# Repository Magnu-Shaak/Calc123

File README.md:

# Numpad
Making a Numpad accessory that also works as a stand-alone calculator!

Features:
- Numberpad (0-9, 4 operations,"=", ".")
    + Has a built in Local Calculator that displays on the OLED
- Custom Shortcuts Layer
- Displays Layer on OLED
    + Use it yourself: Info at [https://github.com/Magnu-Shaak/Calc123/blob/main/oled_extention.md](url)

3d render in Onshape

## BOM
Also available at [https://github.com/Magnu-Shaak/Calc123/blob/main/bom.csv](url)
| Item                      | Quantity | Listed Price | Total Cost | Link                                                                                  | Source        | Notes                                                                    |         |
|---------------------------|----------|--------------|------------|---------------------------------------------------------------------------------------|---------------|--------------------------------------------------------------------------|---------|
| PCB (5 piece)             | 1        | 4            | 5.76       |                                                                                       | JLC PCB       | Together with another order, paying with JLC account (Saves on shipping) |         |
| XIAO RP2040               | 1        | 4.9          | 4.9        | https://www.digikey.com/en/products/detail/seeed-technology-co-ltd/102010428/14672129 | DigiKey       |                                                                          |         |
| Diodes                    | 16       | 0.8          | 0.8        | https://www.digikey.com/en/products/detail/diotec-semiconductor/1N4148/13164514       | DigiKey       |                                                                          |         |
| "Switches                 |          |              |            |                                                                                       |               |                                                                          |         |
| (32 piece)"               | 1        | 10.99        | 10.99      | https://www.amazon.com/gp/aw/d/B09NNN4XPB                                             | Amazon        | Cheaper than AliExpress                                                  |         |
| 0.91 in. OLED (2 piece)   | 1        | 5.99         | 0          | https://www.amazon.com/Dorhea-Display-Module-SSD1306-3-3V-5V/dp/B08F9F8BYB            | Amazon        | Cheaper than Digikey with manu. Shipping. Can pay for myself             |         |
|                           |          |              |            |                                                                                       |               |                                                                          |         |
| Soldering Iron (Pinecil)* | 1        | 39.99        | 39.99      | https://www.amazon.com/PINECIL-Smart-Mini-Portable-Soldering/dp/B096X6SG13            | Amazon        | Cheapest Adjustable Soldering Iron                                       |         |
| Solder (0.5 oz)           | 1        | 2.97         | 2.97       | https://www.digikey.com/en/products/detail/chip-quik-inc/NCSW-031-0-5OZ/13531391      | DigiKey       | 63/37 tin-lead solder (0.031"")                                          |         |
| De-soldering Braid        | 1        | 2.59         | 2.59       | https://www.digikey.com/en/products/detail/chip-quik-inc/SOLDERWICK2-0/14636561       | DigiKey       | 0.08"                                                                    | 5 foot" |
| Soldering Stand & Sponge  | 1        | 3.28         | 3.28       | https://www.digikey.com/en/products/detail/soldered-electronics/555024/29271457       | Digikey       | Soldered Electronics: ""Soldering Iron Stand""                           |         |
|                           |          |              |            |                                                                                       |               |                                                                          |         |
| Case                      | 1        | 3.5          | 0          |                                                                                       | Local Library | $0.05 per gram, will pay for myself                                      |         |
| Key Caps (10 piece)       | 2        | 9.9          | 9.9        | https://www.digikey.com/en/products/detail/adafruit-industries-llc/5039/14313478      | DigiKey       | Adafruit, cheaper than singles                                           |         |
|                           |          |              |            |                                                                                       |               |                                                                          |         |
| M2 screw (16mm)           | 5        | 0.65         | 0.65       | http://digikey.com/en/products/detail/essentra-components/50M020040P016B/26883690     | DigiKey       | Essentra Components, 5th one was 1 cent                                  |         |
| M2 heatset Inserts        | 5        | 1.09         | 1.09       | https://www.digikey.com/en/products/detail/tri-star-industries-inc/M20X157C/13535373  | DigiKey       | Edit 3d model, 5th one was 1 cent                                        |         |
|                           |          |              |            |                                                                                       |               |                                                                          |         |
| DigiKey: Shipping and Tax | 8 (32)   | 9.09         | 10.45      | https://www.digikey.com/ordering/shoppingcart                                         | DigiKey       | Shipping with USPS Ground Advantage (4.99)                               |         |
| Amazon: Shipping and Tax  | s        | 3.82         | 3.82       |                                                                                       | Amazon        | Free shipping with prime                                                 |         |
|                           |          |              |            |                                                                                       |               |                                                                          |         |
| Total                     | 71       | 103.56       | 97.19      |                                                                                       |               |                                                                          |         |

## Demo links

PCB Demo [Link](https://kicanvas.org/?repo=https%3A%2F%2Fgithub.com%2FMagnu-Shaak%2FCalc123%2Ftree%2Fmain%2FPCB)

OnShape Demo [Link](https://cad.onshape.com/documents/84cb760b87cada0103a9576e/w/b2684d83a2c2c7ea59db64e2/e/a0996dbd1c890850b6caf7a1?renderMode=0&uiState=6a6621498755df13821d28c6)
(click on search bar and hit enter again to load properly)

Code is visible under the Firmware folder

## Asembly

BOM (Bill of Materials) - above, or at [https://github.com/Magnu-Shaak/Calc123/blob/main/BOM.csv](url)

0 - Gather your Materials (PCB, Case parts, Devboard, and a usb-c to [something] cable to connect to your computer

1 - Download Circuit Python (v9.2.9) from circuitpython.org for the microcontroller [here](https://adafruit-circuit-python.s3.amazonaws.com)

2 - Download KMK (as .zip) from the kmk_firmware repo on github [here](https://github.com/KMKfw/kmk_firmware)

3 - Download the dependency files from the circuitpython.org/libraries (for the circuit python 9.x version) or from [here](https://github.com/adafruit/Adafruit_CircuitPython_Bundle/releases/download/20260729/adafruit-circuitpython-bundle-9.x-mpy-20260729.zip)

4 - Download "main.py" and "oled_extension.py" from this repo. They are stored under the "Production" Folder

5 - Mount the microcontroller to your computer
    -Hold the 'B' (boot) bottom
    -Connect it to the computer via a usb-c to [anything on your computer] cable
    -Release the 'B' bottom

6 - Upload Circuit Python's .u2f file onto the microcontroller
    -It Should self eject and reconnect as CIRCUITPY

7 - From the kmk_firmware zip file, Upload the "KMK" folder and boot.py into the root of the CIRCUITPY drive

8.5 - If there is not already a "lib" folder in the root of your CIRCUITPY drive, make one

9 - From the circuit python bundle zip file, Upload the "adafruit_bus_device" and "adafruit_display_text" folders and "adafruit_displayio_ssd1306" file into the lib folder of your CIRCUITPY drive

10 - Eject your CIRCUITPY drive, and disconnect your microcontroller from your computer.

11 - Solder your XIAO RP 2040 devboard and 16 diodes (make sure they are oriented correctly) to the back of your PCB

12 - Place the Top Plate onto the front of your PCB, and align it with the mx key switch positions

13 - Solder the Key switches to the PCB on the back. The plate should be supported by the mx switches when you flip back over

14 - Install the Heatset Inserts to the bottom of your Case

15 - Place the PCB and Top Plate onto the supports in the case

16 - Screw the plate onto your PCB

16.5 - Add the Key Caps onto the MX Switches

17 - Slide in the Custom Insert
16 - Connect your Macropad to the computer and begin using it.

## All Images

  Schematic (Controller)

  Schematic (Key Array)

  PCB Design (KiCad)

  PCB Render (KiCad)

  Case (Onshape)

  USB Cutout

  Custom Insert (Onshape)

  Code is under Firmware/main.py and Firmware/oled_extension.py

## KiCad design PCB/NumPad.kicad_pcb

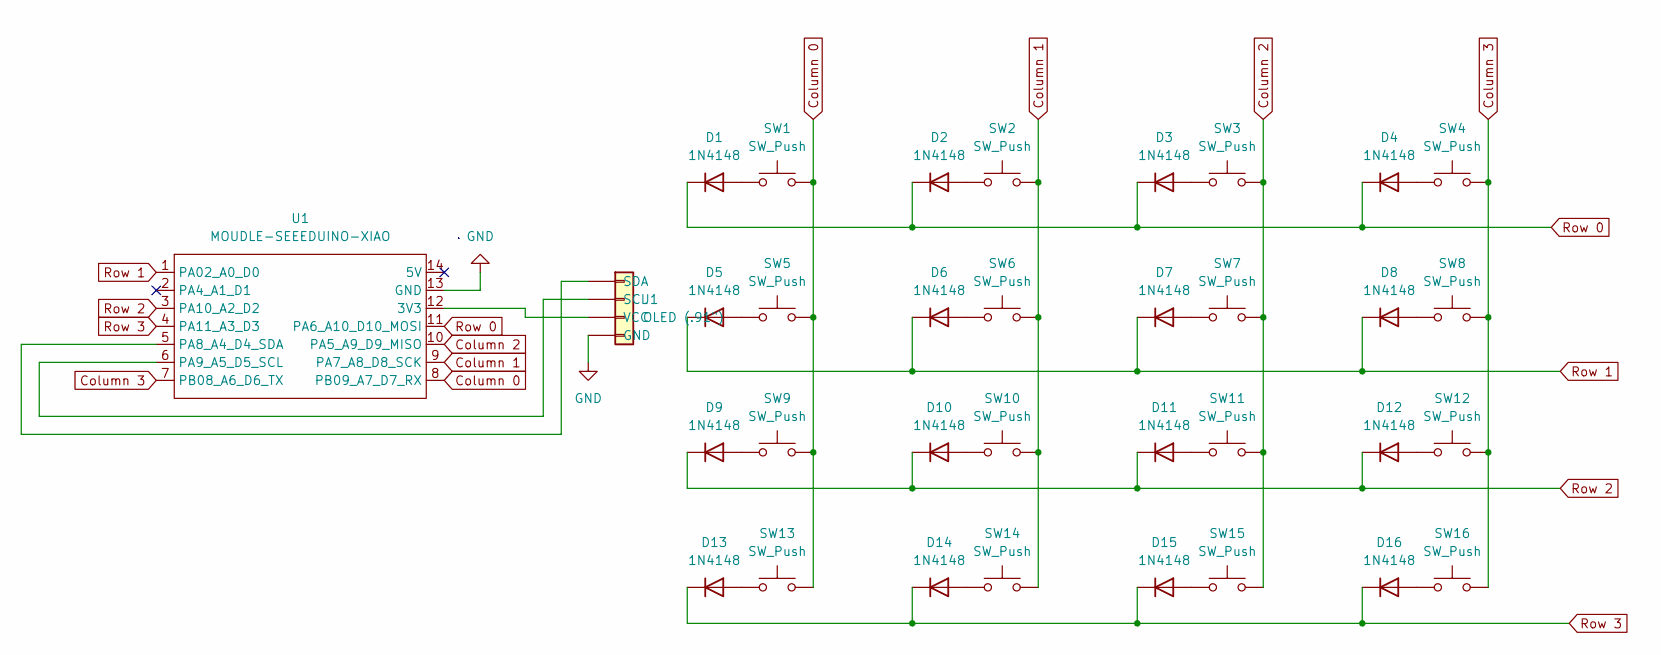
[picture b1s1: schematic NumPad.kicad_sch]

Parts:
D1, D2, D3, D4, D5, D6, D7, D8, D9, D10, D11, D12, D13, D14, D15, D16: 1N4148; D_DO-35_SOD27_P7.62mm_Horizontal
J1: OLED (.91"); 0.91_inch_OLED
SW1, SW2, SW3, SW4, SW5, SW6, SW7, SW8, SW9, SW10, SW11, SW12, SW13, SW14, SW15, SW16: SW_Push; SW_Cherry_MX_1.00u_PCB(1)
U1: MOUDLE-SEEEDUINO-XIAO; XIAO-Generic-Hybrid-14P-2.54-21X17.8MM

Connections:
Column 0: SW1.2, SW5.2, SW9.2, SW13.2, U1.8 (PB09_A7_D7_RX)
Column 1: SW2.2, SW6.2, SW10.2, SW14.2, U1.9 (PA7_A8_D8_SCK)
Column 2: SW3.2, SW7.2, SW11.2, SW15.2, U1.10 (PA5_A9_D9_MISO)
Column 3: SW4.2, SW8.2, SW12.2, SW16.2, U1.7 (PB08_A6_D6_TX)
GND: J1.1 (GND), U1.13 (GND)
unnamed: D1.2 (A), SW1.1
unnamed: D2.2 (A), SW2.1
unnamed: D3.2 (A), SW3.1
unnamed: D4.2 (A), SW4.1
unnamed: D5.2 (A), SW5.1
unnamed: D6.2 (A), SW6.1
unnamed: D7.2 (A), SW7.1
unnamed: D8.2 (A), SW8.1
unnamed: D9.2 (A), SW9.1
unnamed: D10.2 (A), SW10.1
unnamed: D11.2 (A), SW11.1
unnamed: D12.2 (A), SW12.1
unnamed: D13.2 (A), SW13.1
unnamed: D14.2 (A), SW14.1
unnamed: D15.2 (A), SW15.1
unnamed: D16.2 (A), SW16.1
unnamed: J1.3 (SCL), U1.6 (PA9_A5_D5_SCL)
unnamed: J1.4 (SDA), U1.5 (PA8_A4_D4_SDA)
unnamed: J1.2 (VCC), U1.12 (3V3)
Row 0: D1.1 (K), D2.1 (K), D3.1 (K), D4.1 (K), U1.11 (PA6_A10_D10_MOSI)
Row 1: D5.1 (K), D6.1 (K), D7.1 (K), D8.1 (K), U1.1 (PA02_A0_D0)
Row 2: D9.1 (K), D10.1 (K), D11.1 (K), D12.1 (K), U1.3 (PA10_A2_D2)
Row 3: D13.1 (K), D14.1 (K), D15.1 (K), D16.1 (K), U1.4 (PA11_A3_D3)

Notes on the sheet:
GND

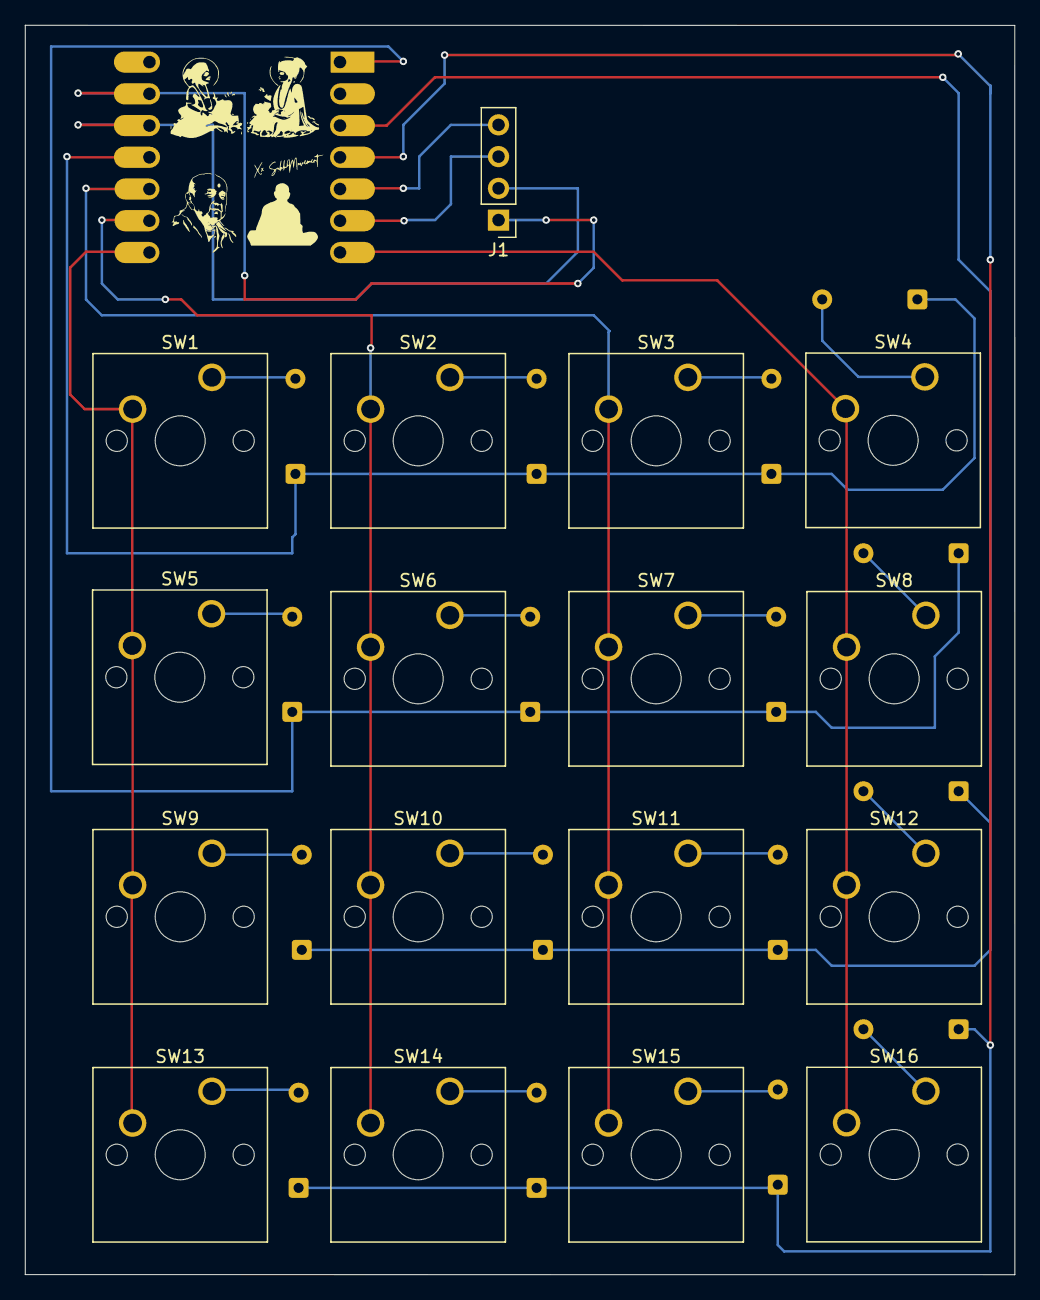
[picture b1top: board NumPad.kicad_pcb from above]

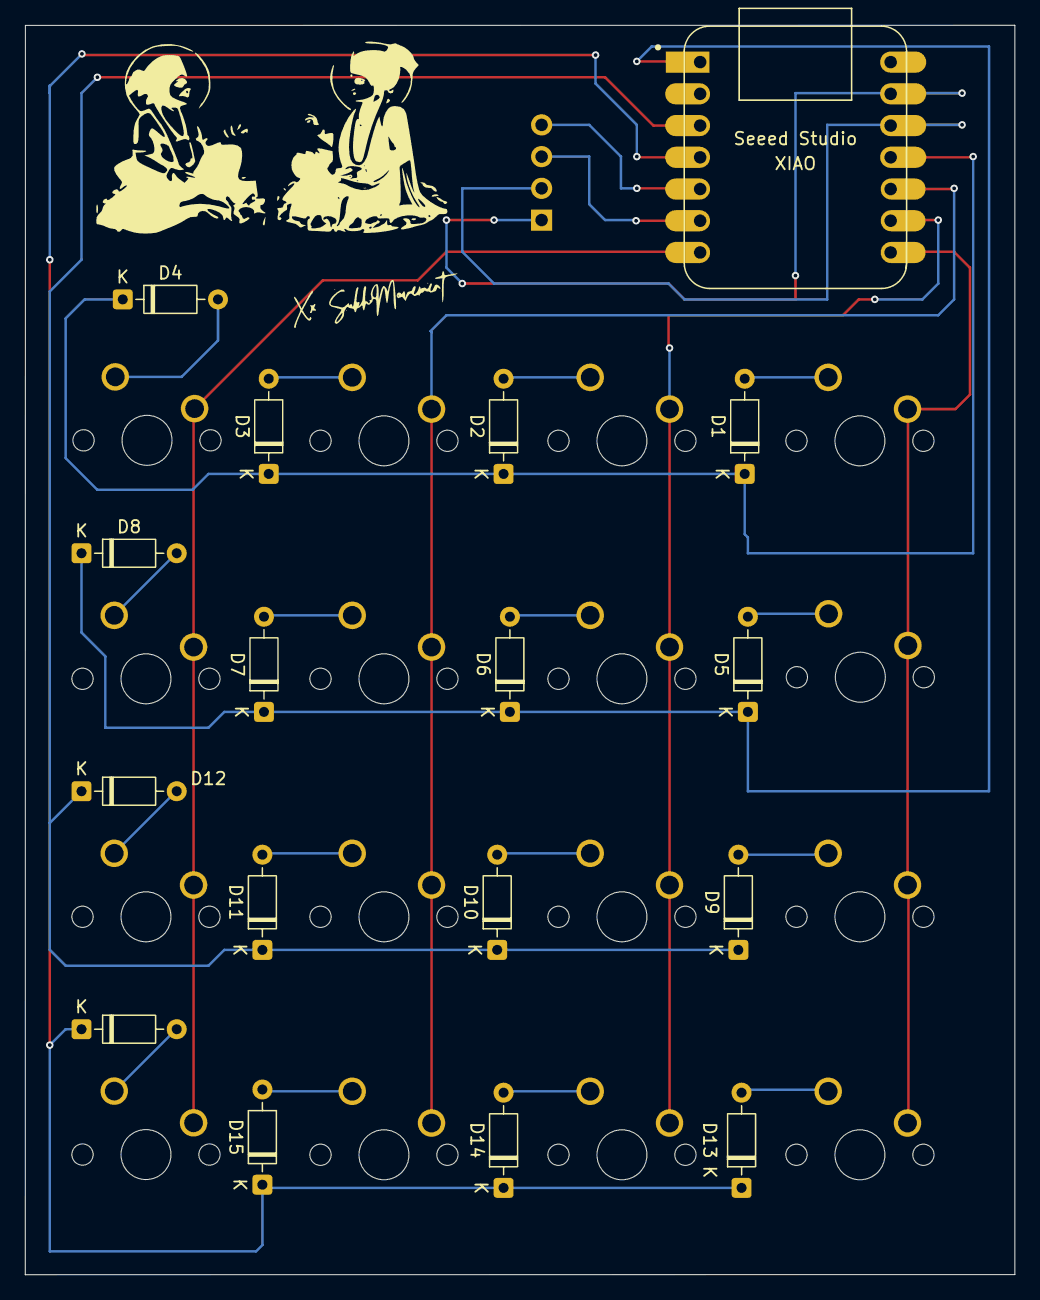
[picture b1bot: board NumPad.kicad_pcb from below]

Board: 2 copper layers, 79.2 x 100.0 mm, 34 parts (17 on the bottom side), 28 nets.
